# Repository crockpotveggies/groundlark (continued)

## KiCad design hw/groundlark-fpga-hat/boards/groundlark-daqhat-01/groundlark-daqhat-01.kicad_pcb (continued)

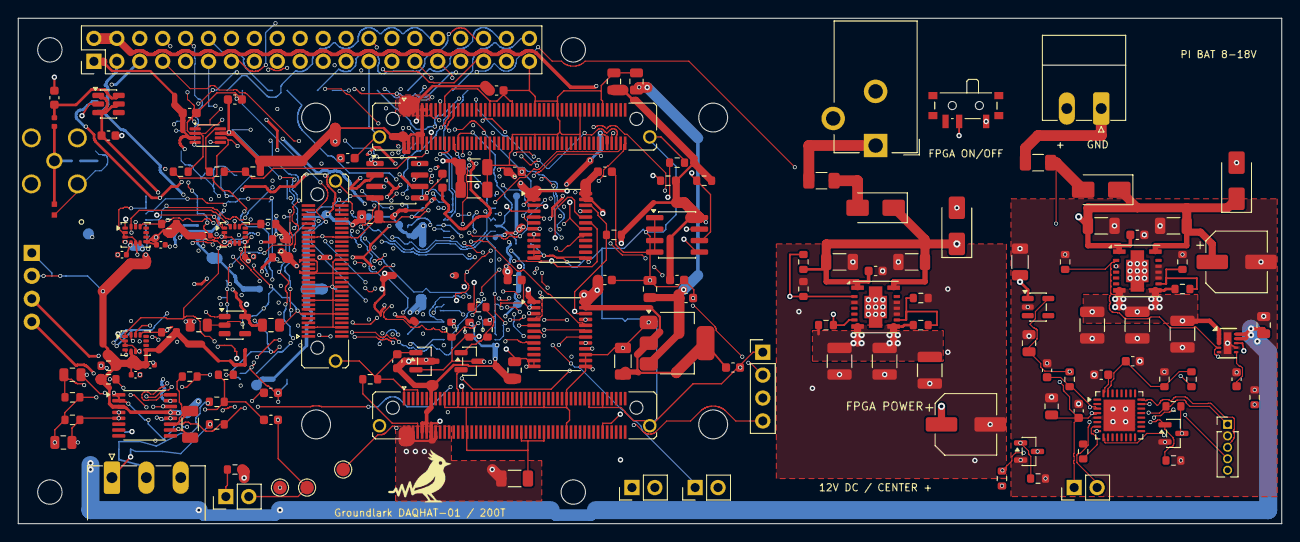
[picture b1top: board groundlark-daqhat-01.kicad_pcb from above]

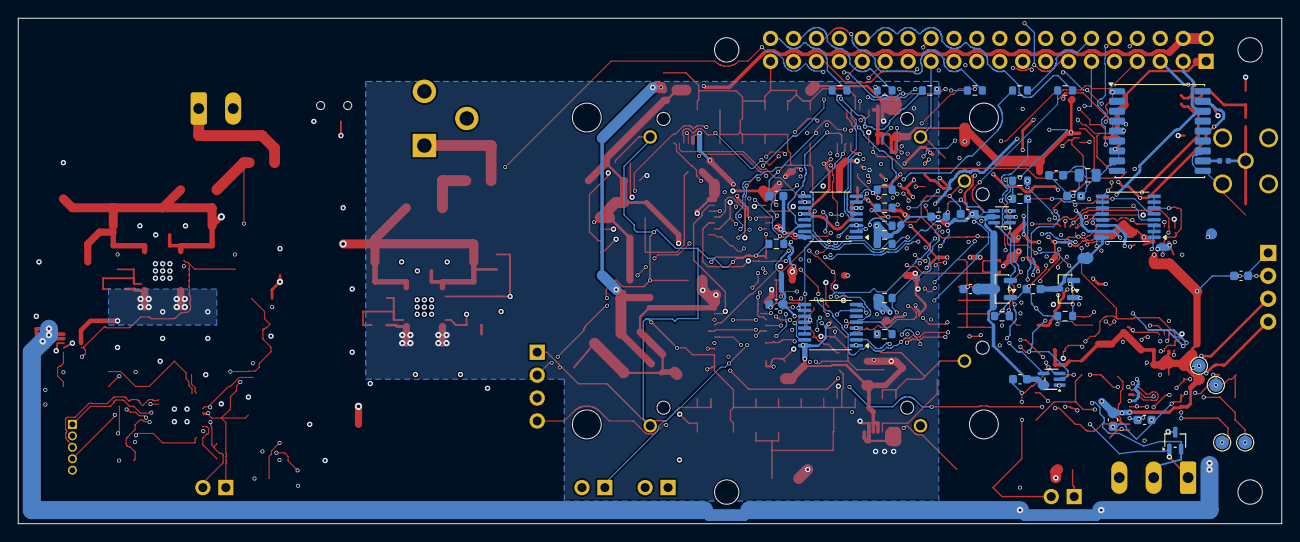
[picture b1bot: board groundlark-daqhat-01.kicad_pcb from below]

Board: 6 copper layers, 140.0 x 56.0 mm, 203 parts (44 on the bottom side), 109 nets.

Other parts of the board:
H1, H2, H3, H4: M2.5 NPTH; MountingHole__MountingHole_2.7mm_M2.5
H80, H81, H82, H83: M3 / 8 mm spacer; TZ_TZ_HOLE

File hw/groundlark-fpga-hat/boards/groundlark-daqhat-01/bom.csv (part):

Reference,Value,MPN,Footprint,DNP,Note
J1,Raspberry Pi 40-pin,Samtec ESQ-120-23-G-D,Connector_PinHeader_2.54mm__PinHeader_2x20_P2.54mm_Vertical,False,"Header land pattern matches bottom mounted socket top-view numbering; tall stack, check Pi 4/5 cooler clearance."
U1,24LC32A,24LC32A-I/SN,Package_SO__SOIC-8_3.9x4.9mm_P1.27mm,False,
R1,3.9k,RC0603FR-073K9L,Resistor_SMD__R_0603_1608Metric,False,
R2,3.9k,RC0603FR-073K9L,Resistor_SMD__R_0603_1608Metric,False,
R3,1k,RC0603FR-071KL,Resistor_SMD__R_0603_1608Metric,False,
JP1,EEPROM write enable,EEPROM write enable,Connector_PinHeader_2.54mm__PinHeader_1x02_P2.54mm_Vertical,False,Fit shunt only while programming ID EEPROM.
C1,100n,GRM188R71H104KA93D,Capacitor_SMD__C_0603_1608Metric,False,
C2,10u,GRM21BR61A106KE19L,Capacitor_SMD__C_0805_2012Metric,False,
C3,10u,GRM21BR61A106KE19L,Capacitor_SMD__C_0805_2012Metric,False,
U11,LSM6DSOTR,LSM6DSOTR,Package_LGA__LGA-14_3x2.5mm_P0.5mm_LayoutBorder3x4y,False,
C12,100n,GRM155R71C104KA88D,Capacitor_SMD__C_0402_1005Metric,False,
C13,100n,GRM155R71C104KA88D,Capacitor_SMD__C_0402_1005Metric,False,
R11,10k,RC0603FR-0710KL,Resistor_SMD__R_0603_1608Metric,False,
U12,LSM6DSOTR,LSM6DSOTR,Package_LGA__LGA-14_3x2.5mm_P0.5mm_LayoutBorder3x4y,False,
C14,100n,GRM155R71C104KA88D,Capacitor_SMD__C_0402_1005Metric,False,
C15,100n,GRM155R71C104KA88D,Capacitor_SMD__C_0402_1005Metric,False,
R12,10k,RC0603FR-0710KL,Resistor_SMD__R_0603_1608Metric,False,
U13,LSM6DSOTR,LSM6DSOTR,Package_LGA__LGA-14_3x2.5mm_P0.5mm_LayoutBorder3x4y,False,
C16,100n,GRM155R71C104KA88D,Capacitor_SMD__C_0402_1005Metric,False,
C17,100n,GRM155R71C104KA88D,Capacitor_SMD__C_0402_1005Metric,False,
R13,10k,RC0603FR-0710KL,Resistor_SMD__R_0603_1608Metric,False,
J4,FPGA test UART/reset,Coldfoot UART service ONLY,Connector_PinHeader_2.54mm__PinHeader_1x04_P2.54mm_Vertical,False,Test points for assembled module UART and active-low reset; do not connect a second driving host.
H1,M2.5 NPTH,M2.5 NPTH,MountingHole__MountingHole_2.7mm_M2.5,False,Nonmagnetic standoffs.
H2,M2.5 NPTH,M2.5 NPTH,MountingHole__MountingHole_2.7mm_M2.5,False,Nonmagnetic standoffs.
H3,M2.5 NPTH,M2.5 NPTH,MountingHole__MountingHole_2.7mm_M2.5,False,Nonmagnetic standoffs.
H4,M2.5 NPTH,M2.5 NPTH,MountingHole__MountingHole_2.7mm_M2.5,False,Nonmagnetic standoffs.
U40,TLV1117LV33DCYR,TLV1117LV33DCYR,Package_TO_SOT_SMD__SOT-223-3_TabPin2,False,
C40,10u,GRM21BR61A106KE19L,Capacitor_SMD__C_0805_2012Metric,False,
C41,100n,GRM188R71H104KA93D,Capacitor_SMD__C_0603_1608Metric,False,
C42,22u,GRM31CR61A226KE19L,Capacitor_SMD__C_1206_3216Metric,False,
C43,100n,GRM188R71H104KA93D,Capacitor_SMD__C_0603_1608Metric,False,
U41,SN74LVC8T245PWR,SN74LVC8T245PWR,Package_SO__TSSOP-24_4.4x7.8mm_P0.65mm,False,
U42,SN74LVC8T245PWR,SN74LVC8T245PWR,Package_SO__TSSOP-24_4.4x7.8mm_P0.65mm,False,
C44,100n,GRM188R71H104KA93D,Capacitor_SMD__C_0603_1608Metric,False,
C45,100n,GRM188R71H104KA93D,Capacitor_SMD__C_0603_1608Metric,False,
C46,100n,GRM188R71H104KA93D,Capacitor_SMD__C_0603_1608Metric,False,
C47,100n,GRM188R71H104KA93D,Capacitor_SMD__C_0603_1608Metric,False,
R50,10k,RC0603FR-0710KL,Resistor_SMD__R_0603_1608Metric,False,
R51,100k,RC0603FR-07100KL,Resistor_SMD__R_0603_1608Metric,False,
U43,ISO1640BDR,ISO1640BDR,Package_SO__SOIC-8_3.9x4.9mm_P1.27mm,False,Power-domain isolation only: grounds are joined. Side-1 VOL max 0.71V requires host VIL >=0.8V; verify Pi revision.
C48,100n,GRM188R71H104KA93D,Capacitor_SMD__C_0603_1608Metric,False,
C49,100n,GRM188R71H104KA93D,Capacitor_SMD__C_0603_1608Metric,False,
R52,4.7k,RC0603FR-074K7L,Resistor_SMD__R_0603_1608Metric,False,
R53,4.7k,RC0603FR-074K7L,Resistor_SMD__R_0603_1608Metric,False,
TP1,SENS_3V3,SENS_3V3,TestPoint__TestPoint_Pad_D1.5mm,False,
TP2,GND,GND,TestPoint__TestPoint_Pad_D1.5mm,False,
TP4,SENSOR_OE_N,SENSOR_OE_N,TestPoint__TestPoint_Pad_D1.5mm,False,
U51,TXU0202DCUR,TXU0202DCUR,Package_SO__VSSOP-8_2.3x2mm_P0.5mm,False,
C75,100n,GRM188R71H104KA93D,Capacitor_SMD__C_0603_1608Metric,False,
C76,100n,GRM188R71H104KA93D,Capacitor_SMD__C_0603_1608Metric,False,
R61,47,RC0603FR-0747RL,Resistor_SMD__R_0603_1608Metric,False,
R62,100k,RC0603FR-07100KL,Resistor_SMD__R_0603_1608Metric,False,
R63,10k,RC0603FR-0710KL,Resistor_SMD__R_0603_1608Metric,False,
U52,TLV803EA30DBZR,TLV803EA30DBZR,Package_TO_SOT_SMD__SOT-23,False,"3.0V falling threshold, 200ms nominal release delay; open-drain output."
C77,100n,GRM188R71H104KA93D,Capacitor_SMD__C_0603_1608Metric,False,
R64,10k,RC0603FR-0710KL,Resistor_SMD__R_0603_1608Metric,False,
Q1,2N7002,2N7002,Package_TO_SOT_SMD__SOT-23,False,Pi GPIO17 HIGH asserts chip reset; does not drive a live voltage into unpowered chip.
R65,1k,RC0603FR-071KL,Resistor_SMD__R_0603_1608Metric,False,
R66,100k,RC0603FR-07100KL,Resistor_SMD__R_0603_1608Metric,False,
J80,LSHM-150-04.0-L-DV-A-S-K-TR,LSHM-150-04.0-L-DV-A-S-K-TR,TZ_TZ100,False,Mates JM1; opposite parity; 8 mm board surface gap
J81,LSHM-150-04.0-L-DV-A-S-K-TR,LSHM-150-04.0-L-DV-A-S-K-TR,TZ_TZ100,False,Mates JM2; opposite parity; 8 mm board surface gap
J82,LSHM-130-04.0-L-DV-A-S-K-TR,LSHM-130-04.0-L-DV-A-S-K-TR,TZ_TZ60,False,Mates JM3; opposite parity; 8 mm board surface gap
JP80,TSW-102-07-G-S,TSW-102-07-G-S,TZ_TZ_JP,False,Fit shunt to DISABLE module; open enables on-board sequence
JP81,TSW-102-07-G-S,TSW-102-07-G-S,TZ_TZ_JP,False,Fit shunt to request module configuration reset
R80,10k,RC0603FR-0710KL,Resistor_SMD__R_0603_1608Metric,False,FPGA JTAG selection / spare CPLD control idle pull-down
R81,10k,RC0603FR-0710KL,Resistor_SMD__R_0603_1608Metric,False,FPGA JTAG selection / spare CPLD control idle pull-down
C80,22u,GRM31CR61A226KE19L,Capacitor_SMD__C_1206_3216Metric,False,Carrier local decoupling; module contains core decoupling
C81,22u,GRM31CR61A226KE19L,Capacitor_SMD__C_1206_3216Metric,False,Carrier local decoupling; module contains core decoupling
C82,22u,GRM31CR61A226KE19L,Capacitor_SMD__C_1206_3216Metric,False,Carrier local decoupling; module contains core decoupling
C83,100n,GRM188R71H104KA93D,Capacitor_SMD__C_0603_1608Metric,False,Carrier local decoupling; module contains core decoupling
C84,4.7u,GRM21BR71A475KA73L,Capacitor_SMD__C_0805_2012Metric,False,Carrier local decoupling; module contains core decoupling
C85,4.7u,GRM21BR71A475KA73L,Capacitor_SMD__C_0805_2012Metric,False,Carrier local decoupling; module contains core decoupling
H80,M3 / 8 mm spacer,M3 / 8 mm spacer,TZ_TZ_HOLE,False,
H81,M3 / 8 mm spacer,M3 / 8 mm spacer,TZ_TZ_HOLE,False,
H82,M3 / 8 mm spacer,M3 / 8 mm spacer,TZ_TZ_HOLE,False,
H83,M3 / 8 mm spacer,M3 / 8 mm spacer,TZ_TZ_HOLE,False,
U22,ADS122C04,ADS122C04IPWR,Package_SO__TSSOP-16_4.4x5mm_P0.65mm,False,"I2C 0x40; internal 2.048V reference, gain 64, normal 330 SPS; unused analog/reference inputs open per TI."
J90,GEO + / - / SHIELD,1803280,"Connector_Phoenix_MC__PhoenixContact_MC_1,5_3-G-3.81_1x03_P3.81mm_Horizontal",False,"Horizontal outward entry (+Y). 1 positive, 2 negative, 3 cable shield. Mate Phoenix 1803581. Never connect power."
D90,TPD2E2U06,TPD2E2U06DCKR,Package_TO_SOT_SMD__SOT-323_SC-70,False,Connector ESD suppression only; not lightning protection.
R90,1k,RC0603FR-071KL,Resistor_SMD__R_0603_1608Metric,False,Matched series input filter / current limiting.
R91,1k,RC0603FR-071KL,Resistor_SMD__R_0603_1608Metric,False,
C90,100n C0G,C3216C0G1H104J160AA,Capacitor_SMD__C_1206_3216Metric,False,C0G differential filter; no piezoelectric X7R on signal path.
C91,1n C0G,C0603C102J5GACTU,Capacitor_SMD__C_0603_1608Metric,False,
C92,1n C0G,C0603C102J5GACTU,Capacitor_SMD__C_0603_1608Metric,False,
R92,1M,RC0603FR-071ML,Resistor_SMD__R_0603_1608Metric,False,
R93,1M,RC0603FR-071ML,Resistor_SMD__R_0603_1608Metric,False,
R94,10k,RC0603FR-0710KL,Resistor_SMD__R_0603_1608Metric,False,
R95,10k,RC0603FR-0710KL,Resistor_SMD__R_0603_1608Metric,False,
C93,10u,GRM21BR61A106KE19L,Capacitor_SMD__C_0805_2012Metric,False,Filtered mid-supply; sensor has no excitation current source.
R96,22,RC0603FR-0722RL,Resistor_SMD__R_0603_1608Metric,False,
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
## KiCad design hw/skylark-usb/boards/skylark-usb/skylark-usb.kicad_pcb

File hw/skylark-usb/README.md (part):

# Skylark USB — Rev A

Skylark is the Groundlark project's outdoor air-quality accessory. Its **90 × 100 mm,
four-layer PCB** mounts vertically inside a ventilated, downward-open hood. Two
removable gas cells face the sheltered air space. A separate PMS5003 sits beside
the board, with its sampling face toward the bottom grille.

The front silkscreen carries the 7 mm Groundlark favicon above the Skylark title.

The atopile circuit, routed KiCad board, review schematic and BOM are implemented.
This is an **engineering prototype**, with [STM32 firmware](../../sw/skylark/README.md)
and shared simulation/tests implemented. Calibration and physical
qualification remain pending; it is not a fabrication release or a validated
volcanic warning instrument. No camera, Pi HAT or separate sensor daughterboard is included.

## Hardware

| Function | Implementation |
| --- | --- |
| USB | USB-C, USB 2.0 full speed; STM32F072CBT6 with internal USB clock |
| SO₂ | SGX-7SO2-AQ-20, separate working/auxiliary TIAs, 100 kΩ feedback |
| H₂S | SGX-7H2S-AQ-25, separate working/auxiliary TIAs, 20 kΩ feedback |
| Gas conversion | ADS122C04, external REF3025 reference, four independent ADC inputs |
| Analog circuits | OPA387/OPA2387, switched analog supply, buffered 1.25 V electrode reference, compensated potentiostats, power-off electrode clamps |
| Particles | External PMS5003; protected switched 5 V supply, UART, sleep/reset control |
| Temperature/humidity | Filtered SHT40-AD1F-R2, I²C 0x44, on a slotted PCB finger near the lower ventilation |
| Pressure | BMP388, I²C 0x76 |
| Debug/service | 10-pin 1.27 mm SWD, reset/boot buttons, status LED and seven rail test pads |

Gas channels use 20 Ω electrode loads and 0.1%, 25 ppm/K thin-film gain resistors.
SO₂ feedback is 100 kΩ/100 nF; H₂S feedback is 20 kΩ/500 nF (five parallel
100 nF capacitors). Feedback and potentiostat compensation use C0G dielectric
to avoid the piezoelectric behavior of high-permittivity ceramic capacitors.
Each ADC input has a 10 kΩ/10 µF filter placed beside the ADC. Both gases have
a nominal 15.9 Hz feedback pole and a 1.59 Hz output pole. Together they attenuate a 50 Hz input signal
by about 40.3 dB before the ADC's digital filtering. These calculations omit cell
impedance, capacitor bias/temperature effects and amplifier noise gain; they
do not establish loop stability or a noise floor. Preserve matching WE/AE filters.

OPA387/OPA2387 specifies 177 nV peak-to-peak input noise over 0.1–10 Hz. Short,
via-free summing traces, local feedback and bypass returns reduce avoidable
pickup. The ADS122C04's typical ±5 nA bypass-mode input current can produce
about ±50 µV across 10 kΩ; this is a typical error estimate, not a guaranteed
bound. Measure channel offset and its drift, and retain calibration metadata.

Both outer faces have guard copper driven from the 1.25 V reference through
100 Ω R75. Exposed guard arcs surround the working, reference and auxiliary
socket pads; gaps allow signal traces to exit. Cleanliness remains essential:
4 nA of parasitic current mimics 10 ppb SO₂ at nominal sensitivity. Qualify
residual leakage after assembly, cleaning and coating, including humid soak
and fan-on/fan-off tests. Mask and coating alone do not establish that limit.

Both reference and working electrodes are nominally at 1.25 V;
this is a **zero-bias assumption**. SGX's public AQ datasheets do not unambiguously
specify bias for both exact variants. Obtain SGX confirmation before releasing
the circuit for fabrication. The manufacturer cell drawing is a bottom view;
the PCB socket pattern explicitly mirrors it.

Nominal sensitivity is 40 mV/ppm for SO₂ and 34 mV/ppm for H₂S. At the published
maximum sensitivity, full-scale gas excursions are approximately 1.00 V and
1.05 V around 1.25 V, respectively. These are headroom calculations, not detection
limits. Preserve raw WE and AE readings; compensation coefficients and baseline
calibration must come from measurements for each cell. A 24-bit ADC does not
establish ppb-level system accuracy.

## Assembly and installation

The [Skylark procurement registry](../assembly/skylark-usb/jlcpcb-parts.json)
covers all 119 PCB assembly placements in 37 exact manufacturer/catalog groups,
with dated stock observations in the registry. The current assembly uses
HRO TYPE-C-31-M-12 / C165948, Yageo RC0603FR-0782KL / C137678 and Bosch
BMP388 / C779278. These replacements were available without preorder, with a
minimum quantity of one, on 2026-09-28 UTC. Public stock is not reserved stock.
C2 retains its documented 16 V Murata 4.7 µF procurement substitution.

The [assembly guide](../assembly/skylark-usb/README.md) describes the read-only
Gerber/BOM/CPL exporter and manual parts. All 119 placements pass the numbered
supplier-pad fit, including explicit bottom-side handling. The HRO footprint
uses the manufacturer's 2020-12-08 drawing, shared power lands and plated shell
slots. Gas cells, eight sockets and the PMS5003 harness are assembled separately.
Recheck stock and both sides of the actual order preview before purchasing.

- Order JLCPCB's standard **1.6 mm, four-layer FR-4, JLC04161H-7628** stack:
  1 oz outer copper and 0.5 oz inner copper, with both inner layers assigned to
  ground. The recorded dielectric thicknesses are 0.2104 / 1.065 / 0.2104 mm.
  Use ENIG and conventional tented **0.60/0.30 mm through-vias** outside SMT pads.
  Minimum track/clearance is 0.15 mm. This design does not require HDI, blind or
  buried vias, filled/capped vias, or custom lamination. The stack comes from
  [JLCPCB's stock table](https://jlcpcb.com/impedance); USB signal integrity still
  requires a physical check. The selection does not imply an impedance guarantee.
- Fit **eight Mill-Max 0322-0-15-15-34-27-10-0 sockets** before inserting the cells.
  Finished socket holes are 2.35 mm nominal. The contact range covers the SGX
  1.00 ± 0.15 mm pins. Do not solder the gas cells directly. Check actual insertion
  and retention using purchased parts; provide a removable enclosure retainer.
- Gas-cell bodies are Ø31.5 × 15.5 mm. With the socket rim 4.88 mm above the PCB
  seating surface (including its 0.81 mm flange), allow at least 20.38 mm on the cell side, plus assembly tolerance and airflow
  clearance. The centers are 42 mm apart. Keep sensor faces clear.
- Four 3.2 mm mounting holes are at (4,4), (86,4), (4,96), (86,55) mm from the
  upper-left outline corner. USB and the temperature-sensor finger face down.
  The PMS5003 needs its own cradle and cable restraint.
- J2 is a **JST GH 8-pin board connector**. A harness must map its numbered pins
  to the PMS5003; do not assume an arbitrary supplied PMS cable mates with this
  header or preserves wire order.
- Clean and dry the PCB before installing cells. Conformal coating must exclude
  gas-cell faces and socket contacts, the SHT40 filter, BMP388 pressure port,
  connectors, buttons and service pads. Follow manufacturer assembly instructions;
  do not wash the installed humidity sensor or seal its filter.
- The hood provides rain shielding while admitting ambient air. Coating is an
  additional protection measure, not a waterproof enclosure. Avoid trapped water,
  direct spray, insects and condensation. Keep the PMS exhaust away from the
  temperature sensor and allow passive air exchange around both gas cells.

| J2 pin | Signal | Direction relative to Skylark |
| --- | --- | --- |
| 1 | Switched 5 V | Output |
| 2 | Ground | Return |
| 3 | PMS SET, low for sleep | Open-drain control |
| 4 | PMS RX | UART output to sensor |
| 5 | PMS TX | UART input from sensor |
| 6 | PMS RESET, active low | Open-drain control |
| 7, 8 | Reserved | Deliberately unconnected |

## Power and firmware requirements

The [prototype STM32 firmware](../../sw/skylark/README.md) implements sensor
readout, USB streaming and power sequencing. Its image builds and native fault
tests pass; the following physical power/timing checks remain required.

The PMS rail defaults off. Firmware must enumerate and obtain its configured USB
power allocation before enabling it. The 82 kΩ TPS2553 setting gives approximately
284–369 mA current-limit bounds including resistor tolerance, with 323 mA nominal.
Budget another 50 mA for the controller and supporting circuits; the configured
envelope stays below 500 mA. Measure fan startup, fuse drop and actual consumption;
these are design bounds, not bench results. See the [power supply guide](../../docs/power-supplies.md)
for allocations, cable-voltage cases, attach charge, regulator dissipation and
suspend limits. The analog rail has an 8 mA design
budget. The 22 Ω supply filter leaves at least 3.05 V using the stated regulator
and resistor limits; measure this rail over supply and temperature.

The PMS5003 requires at least 4.5 V at its supply. This board does not boost a low
USB voltage. Use a suitable 5 V source and short cable, verify J2 under load, and
invalidate PM measurements on undervoltage or switch fault. The MCU measures the
post-fuse USB rail through a 2:1 divider. Keep the PMS UART output low or high
impedance while that sensor is unpowered to prevent backfeed. Suspend handling
must turn off the PMS and the analog rail, disable the status LED, and put the
MCU and remaining sensors into suitable low-power states. Measure total current
against the applicable USB suspend budget.

The analog rail defaults off through U13 (TPS22918); electrode clamps default
engaged through Q7. PB12 drives ANA_EN, and PB13 drives CLAMP_HOLD (high engages
the clamps). Keep CLAMP_HOLD high while enabling ANA_EN; after the rail and
reference settle, drive CLAMP_HOLD low to release the clamps. Before disabling
ANA_EN, stop conversions and drive CLAMP_HOLD high. Do not sample until the cell
baseline has settled after restarting. Qualify this sequence, reset/brownout
behavior and the clamp gate voltage on hardware. The 10 nF CT capacitor controls
switch slew; firmware timing must account for the measured rail/reference rise.

Q7 is an MMBT3904 with its emitter at VZERO, so an engaged clamp follows the
electrode reference instead of pulling the JFET gates below powered electrodes.
R74 limits base current. D4 isolates the gate pull-up from a falling USB rail;
R71 returns the gate toward VZERO when that supply disappears. Q1–Q4 are
MMBFJ270 devices, specified at 200 pA maximum gate leakage at 25 °C under the
datasheet test conditions. This is not an outdoor-temperature leakage guarantee.
Check gate-to-electrode voltage and discharge behavior during slow ramps,
hard disconnects, MCU reset and brownout with real cells attached.

Sensor power follows USB configuration and suspend state. Closing a CDC data
session leaves the gas bias active; reopening does not repeat conditioning.
The firmware's 60-second gas suppression is a minimum prototype policy. It does
not certify a stable baseline; field software must apply a qualified settling
and calibration policy before interpreting raw readings as gas concentrations.

Use ADS122C04 address 0x40, gain 1, PGA bypassed and the external 2.5 V reference.
Multiplex AIN0–3 as single-ended SO₂ WE, SO₂ AE, H₂S WE, H₂S AE. Start with normal
330 SPS single-shot conversion mode. Eight-millisecond service slots give a
nominal 32 ms period per electrode (31.25 samples/s). The scheduler budgets
100 kHz I²C transactions and enforces a separate five-tick minimum after a new
conversion starts. Service delays extend the schedule rather than restarting
unfinished conversions. Maintain cell bias during normal operation and treat
power-up settling as missing data.

The 15.9 Hz feedback pole and 1.59 Hz output pole provide approximately 33 dB
nominal attenuation at 31.25 Hz. The output filters use 10 kΩ / 10 µF; effective
capacitance under voltage, temperature and aging must be measured. All original
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
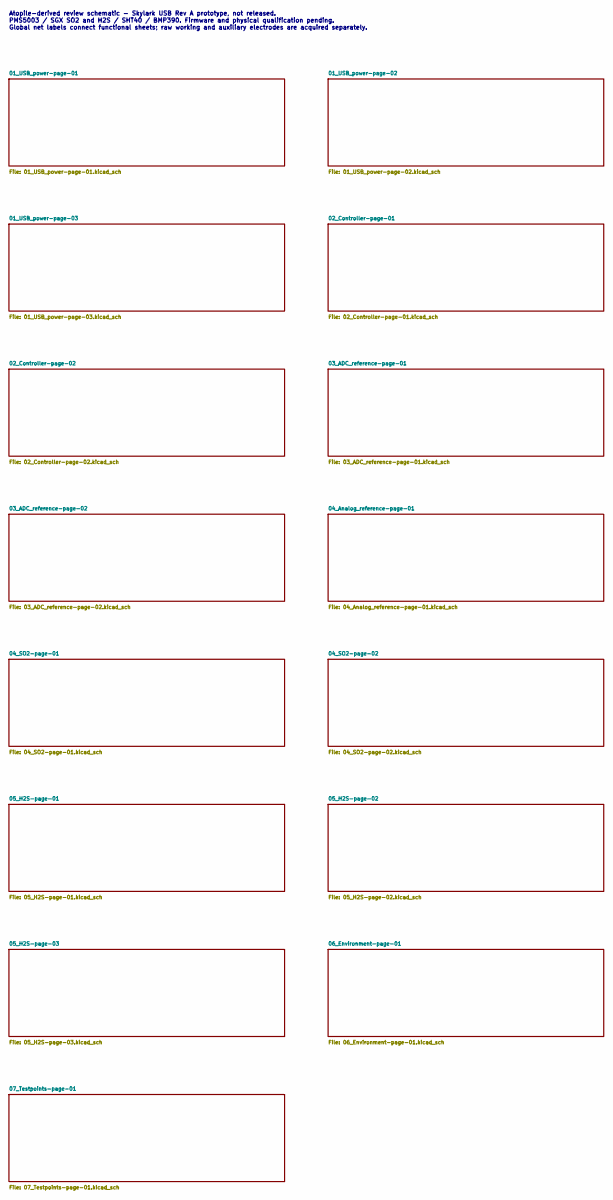
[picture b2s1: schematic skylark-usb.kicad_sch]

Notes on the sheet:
Atopile-derived review schematic - Skylark USB Rev A prototype, not released. PMS5003 / SGX SO2 and H2S / SHT40 / BMP390. Firmware and physical qualification pending. Global net labels connect functional sheets; raw working and auxiliary electrodes are acquired separately.

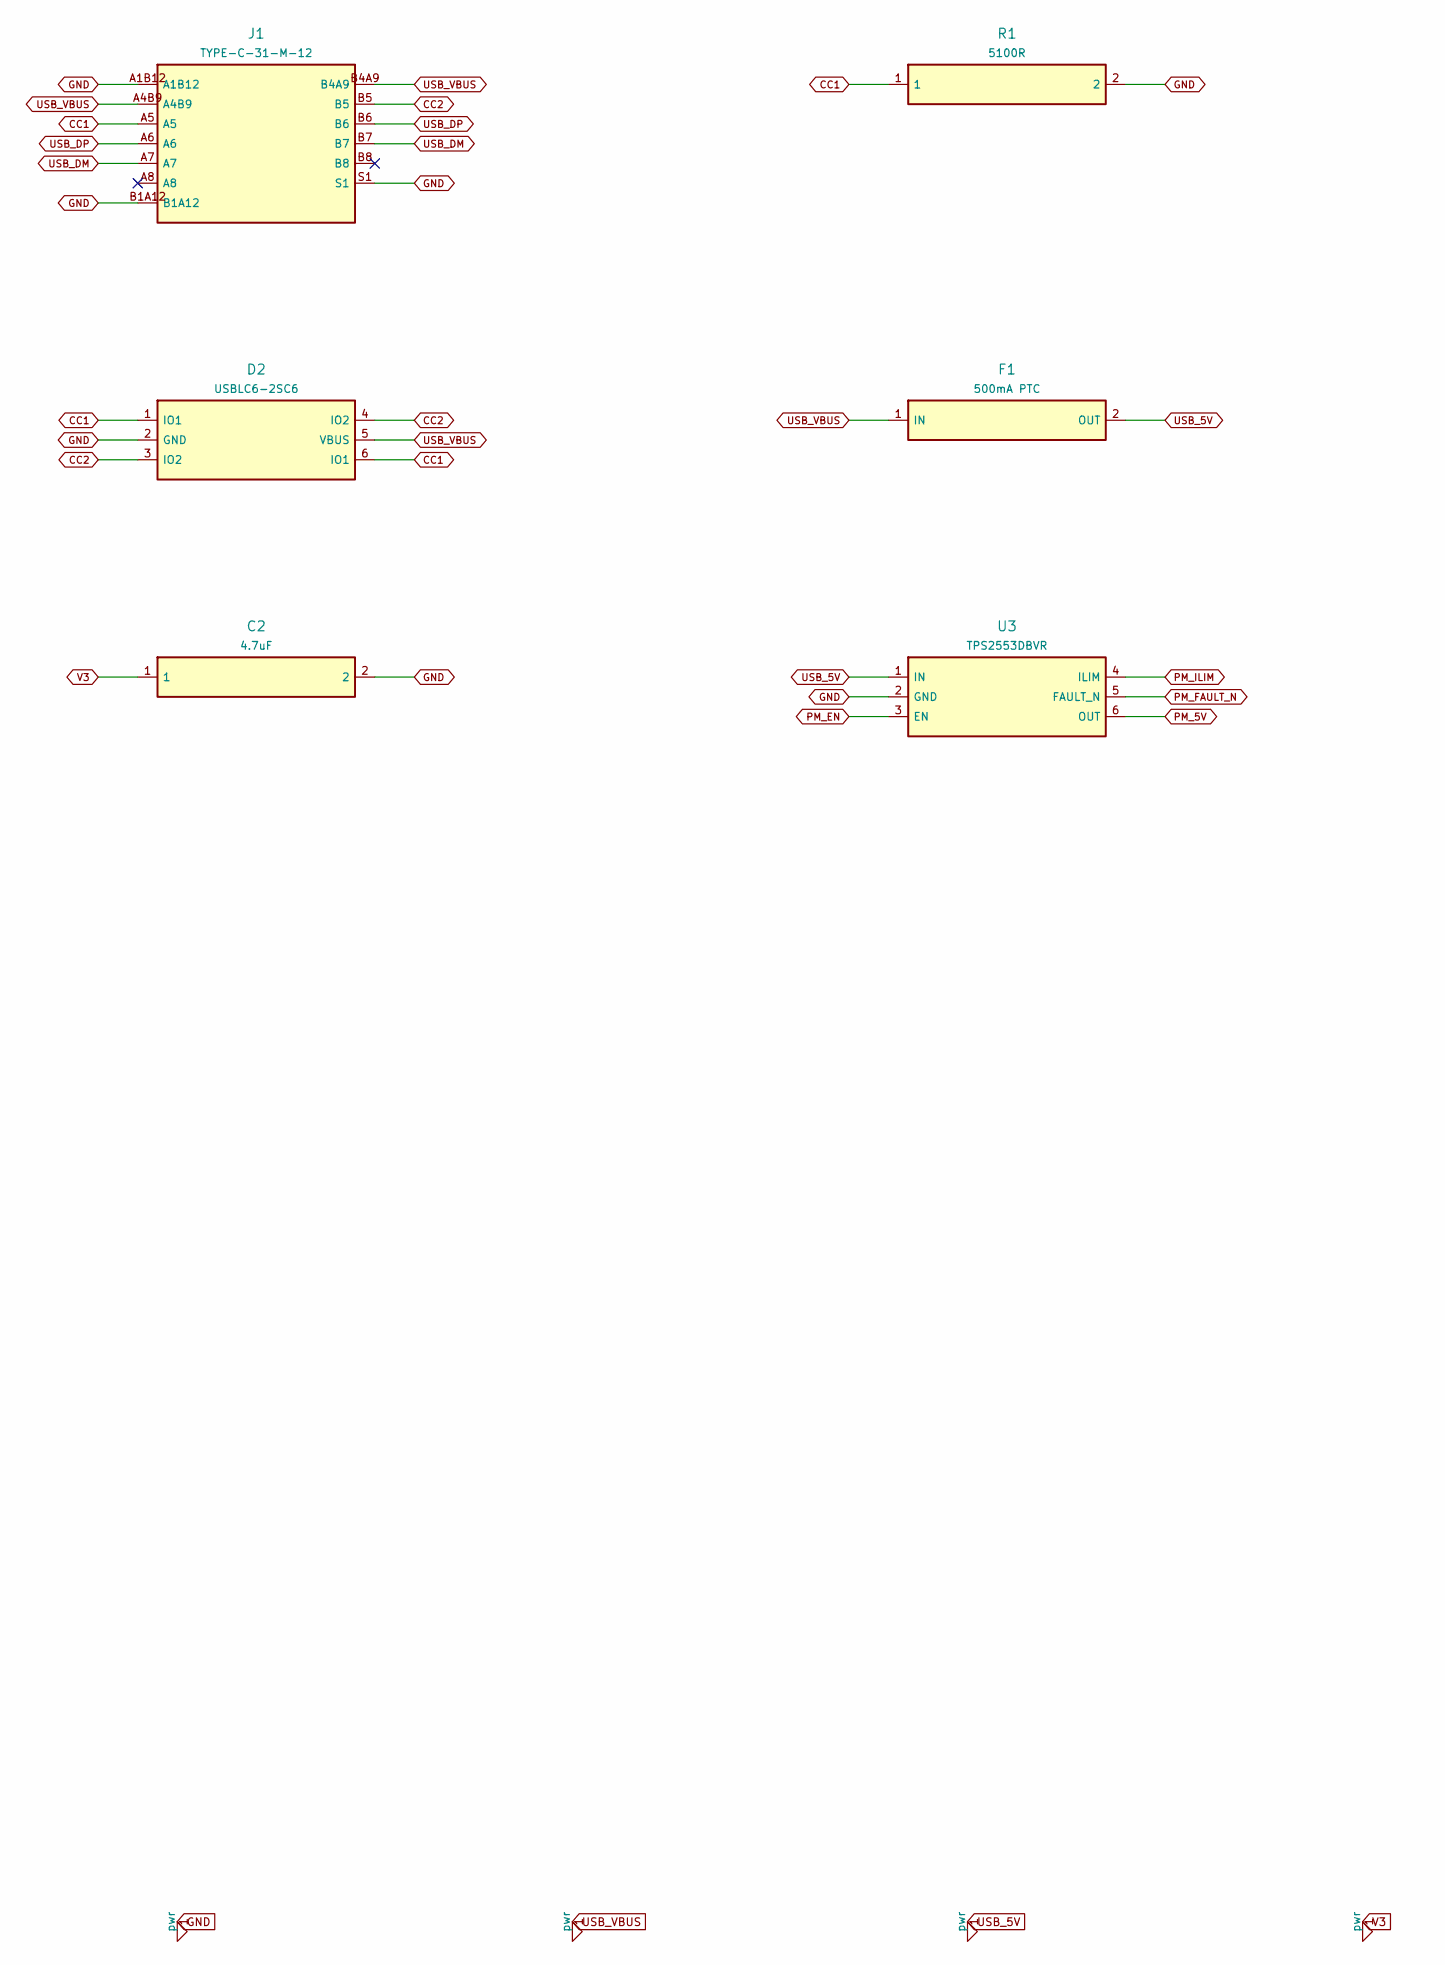
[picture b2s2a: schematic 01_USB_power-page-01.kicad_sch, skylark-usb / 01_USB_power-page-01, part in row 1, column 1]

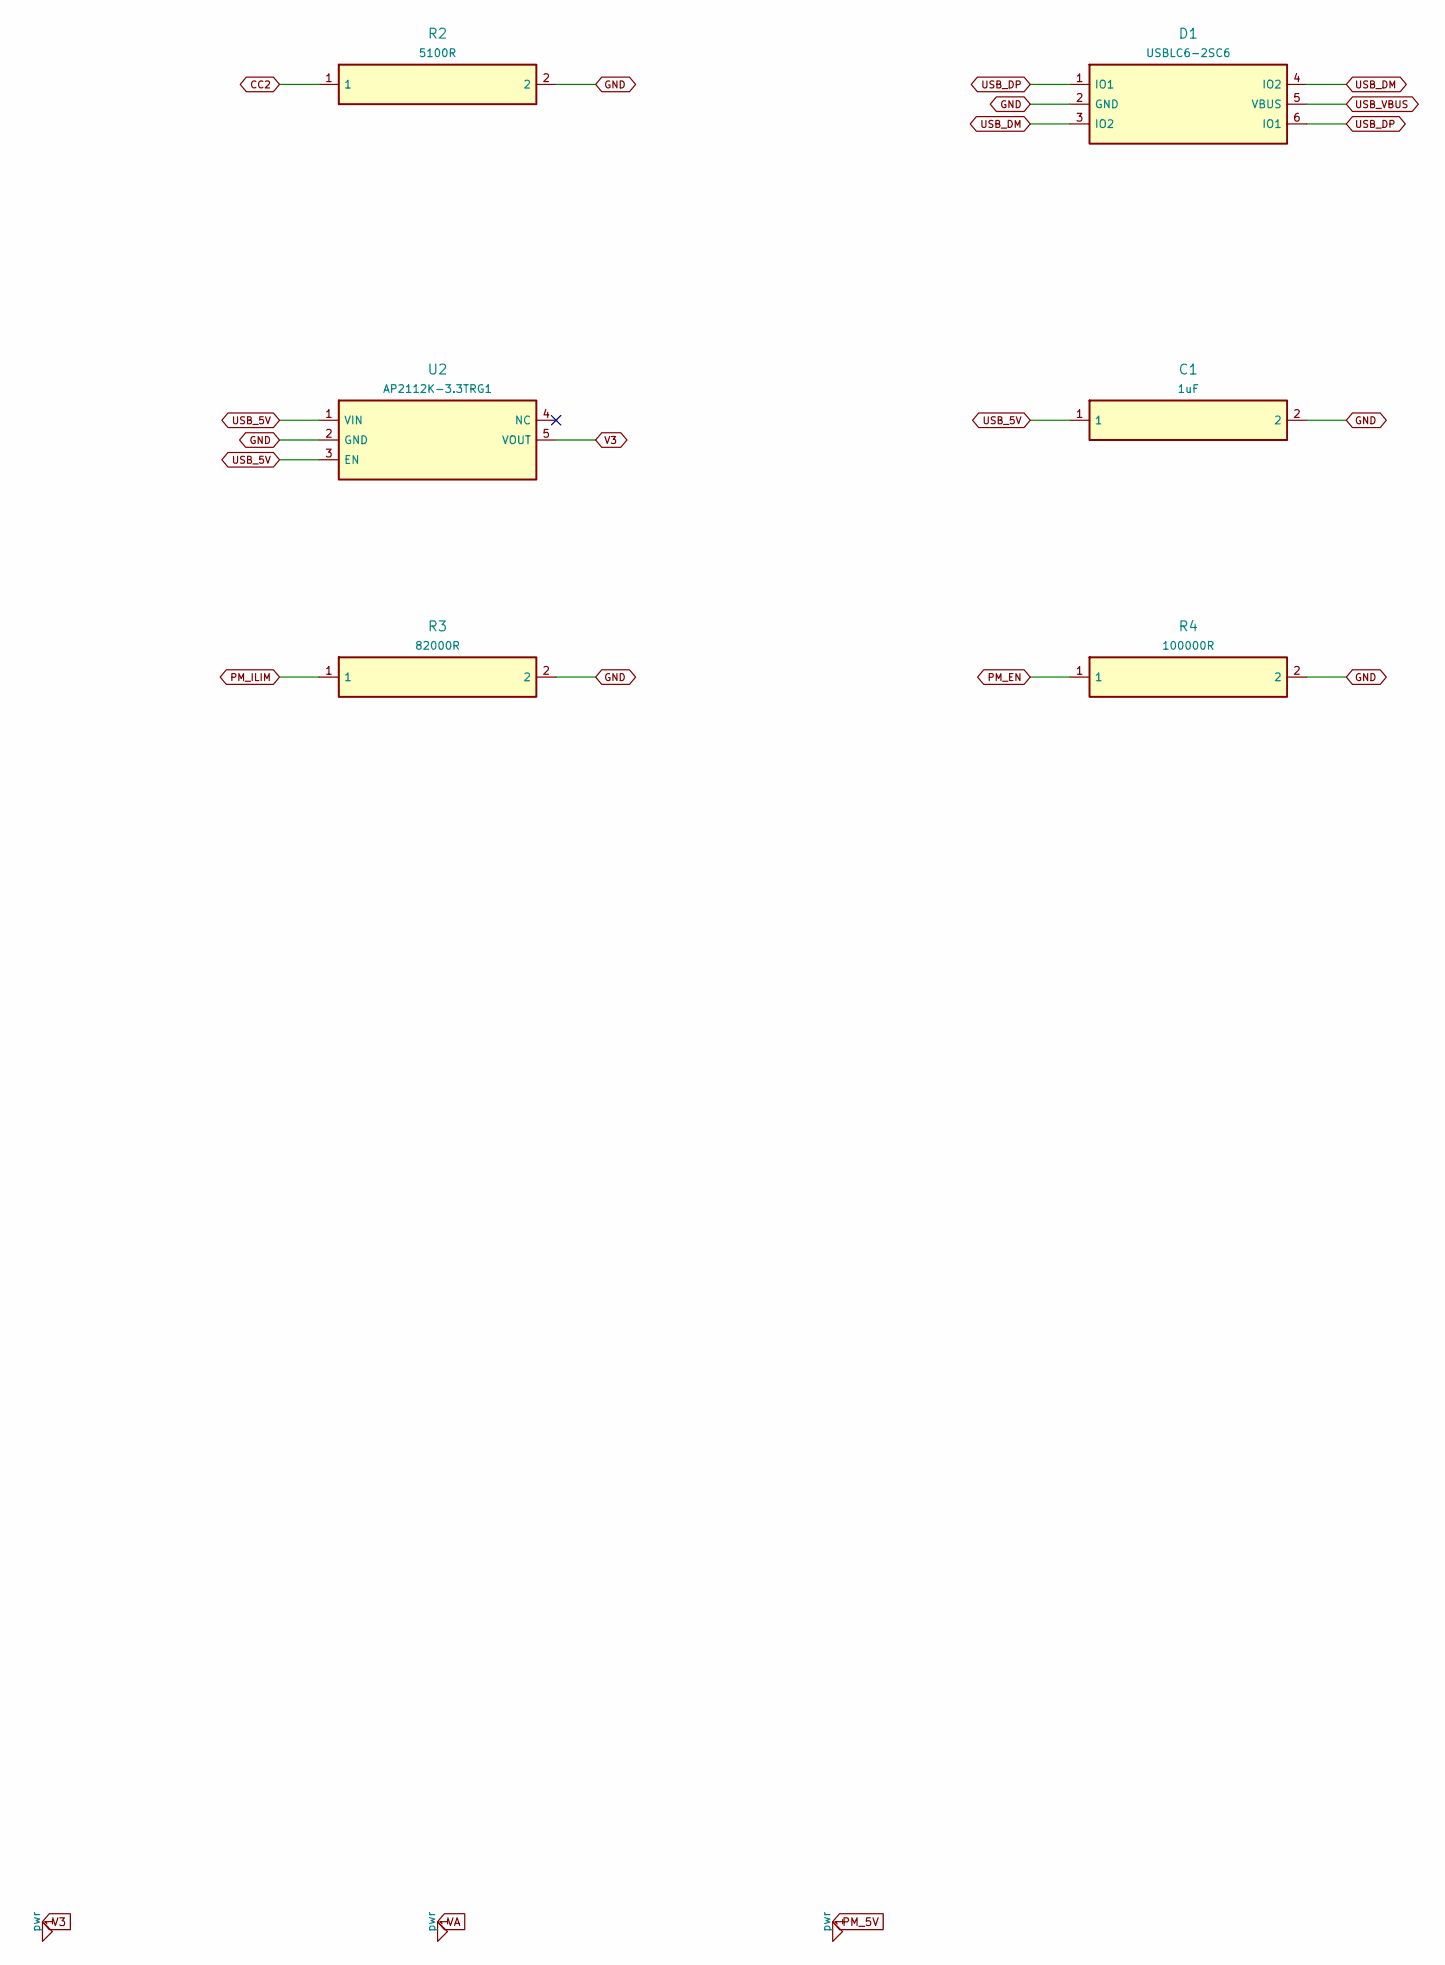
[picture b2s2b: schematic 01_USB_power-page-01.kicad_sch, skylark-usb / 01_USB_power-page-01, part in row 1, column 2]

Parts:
C1: 1uF; Capacitor_SMD__C_0603_1608Metric; MPN GRM188R71E105KA12D
C2: 4.7uF; Capacitor_SMD__C_0805_2012Metric; MPN GRM21BR71A475KA73L
D1, D2: USBLC6-2SC6; Package_TO_SOT_SMD__SOT-23-6; MPN USBLC6-2SC6
F1: 500mA PTC; Fuse_1206; MPN 1206L050YR
J1: TYPE-C-31-M-12; USB_C_HRO_TYPE-C-31-M-12; MPN TYPE-C-31-M-12
R1, R2: 5100R; Resistor_SMD__R_0603_1608Metric; MPN RC0603FR-075K1L
R3: 82000R; Resistor_SMD__R_0603_1608Metric; MPN RC0603FR-0782KL
R4: 100000R; Resistor_SMD__R_0603_1608Metric; MPN RT0603BRD07100KL
U2: AP2112K-3.3TRG1; Package_TO_SOT_SMD__SOT-23-5; MPN AP2112K-3.3TRG1
U3: TPS2553DBVR; Package_TO_SOT_SMD__SOT-23-6; MPN TPS2553DBVR

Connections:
A8: J1.A8
B8: J1.B8
CC1: D2.1 (IO1), D2.6 (IO1), J1.A5, R1.1
CC2: D2.3 (IO2), D2.4 (IO2), J1.B5, R2.1
GND: C1.2, C2.2, D1.2 (GND), D2.2 (GND), J1.A1B12, J1.B1A12, J1.S1, R1.2, R2.2, R3.2, R4.2, U2.2 (GND), U3.2 (GND); also elsewhere on the board
PM_5V: U3.6 (OUT); also elsewhere on the board
PM_EN: R4.1, U3.3 (EN); also elsewhere on the board
PM_FAULT_N: U3.5 (FAULT_N); also elsewhere on the board
PM_ILIM: R3.1, U3.4 (ILIM)
USB_5V: C1.1, F1.2 (OUT), U2.1 (VIN), U2.3 (EN), U3.1 (IN); also elsewhere on the board
USB_DM: D1.3 (IO2), D1.4 (IO2), J1.A7, J1.B7; also elsewhere on the board
USB_DP: D1.1 (IO1), D1.6 (IO1), J1.A6, J1.B6; also elsewhere on the board
USB_VBUS: D1.5 (VBUS), D2.5 (VBUS), F1.1 (IN), J1.A4B9, J1.B4A9
V3: C2.1, U2.5 (VOUT); also elsewhere on the board
u2-4: U2.4 (NC)

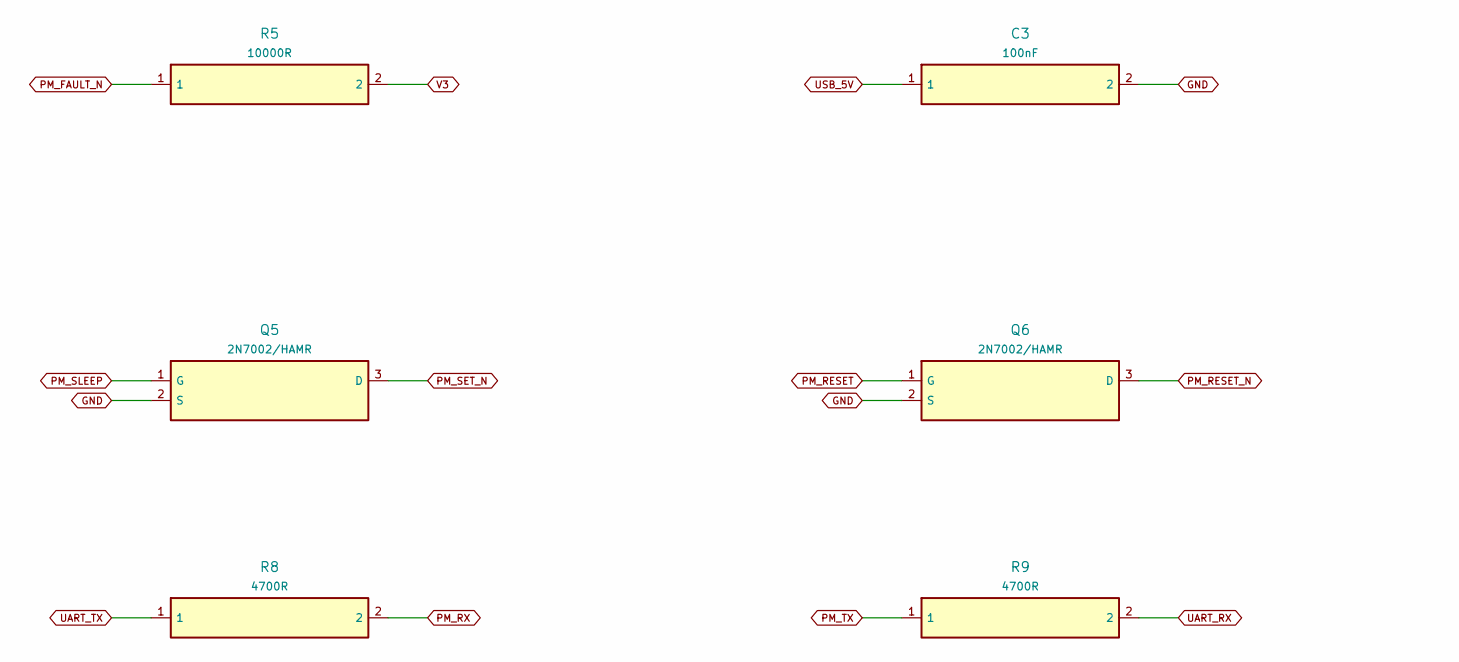
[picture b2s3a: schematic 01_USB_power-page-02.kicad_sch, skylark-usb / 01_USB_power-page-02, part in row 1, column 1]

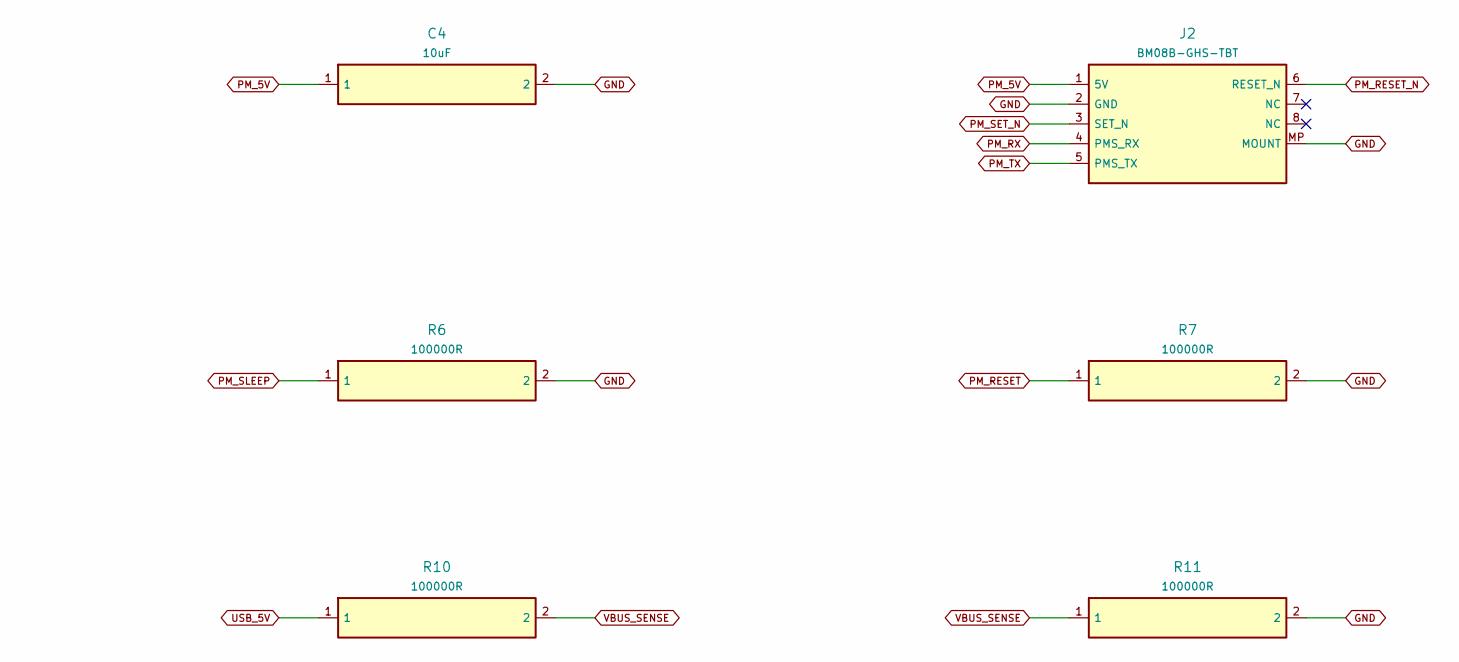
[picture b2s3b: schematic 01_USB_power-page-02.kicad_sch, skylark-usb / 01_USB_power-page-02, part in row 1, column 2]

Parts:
C3: 100nF; Capacitor_SMD__C_0603_1608Metric; MPN GRM188R71H104KA93D
C4: 10uF; Capacitor_SMD__C_0805_2012Metric; MPN GRM21BR61A106KE19L
J2: BM08B-GHS-TBT; Connector_JST__JST_GH_BM08B-GHS-TBT_1x08-1MP_P1.25mm_Vertic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; MPN BM08B-GHS-TBT
Q5, Q6: 2N7002/HAMR; Package_TO_SOT_SMD__SOT-23; MPN 2N7002/HAMR
R5: 10000R; Resistor_SMD__R_0603_1608Metric; MPN RT0603BRD0710KL
R6, R7, R10, R11: 100000R; Resistor_SMD__R_0603_1608Metric; MPN RT0603BRD07100KL
R8, R9: 4700R; Resistor_SMD__R_0603_1608Metric; MPN RC0603FR-074K7L

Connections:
7: J2.7 (NC)
8: J2.8 (NC)
GND: C3.2, C4.2, J2.2 (GND), J2.MP (MOUNT), Q5.2 (S), Q6.2 (S), R6.2, R7.2, R11.2; also elsewhere on the board
PM_5V: C4.1, J2.1 (5V); also elsewhere on the board
PM_FAULT_N: R5.1; also elsewhere on the board
PM_RESET: Q6.1 (G), R7.1; also elsewhere on the board
PM_RESET_N: J2.6 (RESET_N), Q6.3 (D)
PM_RX: J2.4 (PMS_RX), R8.2
PM_SET_N: J2.3 (SET_N), Q5.3 (D)
PM_SLEEP: Q5.1 (G), R6.1; also elsewhere on the board
PM_TX: J2.5 (PMS_TX), R9.1
UART_RX: R9.2; also elsewhere on the board
UART_TX: R8.1; also elsewhere on the board
USB_5V: C3.1, R10.1; also elsewhere on the board
V3: R5.2; also elsewhere on the board
VBUS_SENSE: R10.2, R11.1; also elsewhere on the board

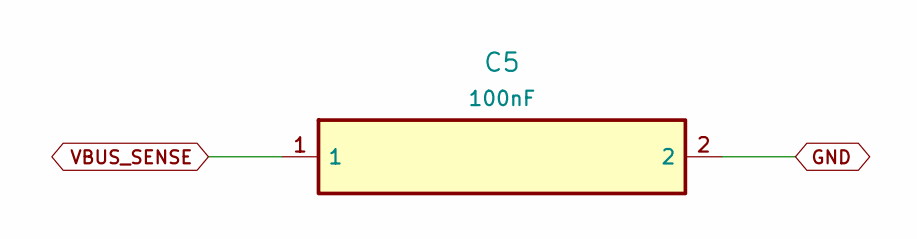
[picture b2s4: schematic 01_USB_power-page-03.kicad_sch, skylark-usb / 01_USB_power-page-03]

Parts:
C5: 100nF; Capacitor_SMD__C_0603_1608Metric; MPN GRM188R71H104KA93D

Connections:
GND: C5.2; also elsewhere on the board
VBUS_SENSE: C5.1; also elsewhere on the board

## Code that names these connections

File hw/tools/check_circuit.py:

"""Independent circuit invariants against the actual atopile-compiled PCB."""
from pathlib import Path
from project_paths import compiled_dir, load_layout
from burrowlark_checks import population
import argparse,json,re
import pcbnew as p
ROOT=Path(__file__).resolve().parents[2]
def require(pins,ref,expected):
    for pin,net in expected.items():
        assert pins.get((ref,str(pin)))==net,(ref,pin,pins.get((ref,str(pin))),net)
def main(boards=('groundlark-field-head',)):
    metadata=load_layout(*boards);source=(ROOT/'hw/shared/elec/parts.ato').read_text() + '\n' + (ROOT/'hw/shared/elec/burrowlark.ato').read_text()
    blocks={m[1]:m[2] for m in re.finditer(r'^component (\w+):\n(.*?)(?=^component |\Z)',source,re.M|re.S)}
    reports=[]
    for name,meta in metadata.items():
        target='field_head';b=p.LoadBoard(str(compiled_dir(target)/(target+'.kicad_pcb')))
        pins={(f.GetReference(),pad.GetNumber()):pad.GetNetname() for f in b.GetFootprints() for pad in f.Pads() if pad.GetNumber()}
        for part in meta['parts']:
            if not part['type']:continue
            block=blocks[part['type']]
            assert f'partnumber="{part["mpn"]}"' in block,(part['ref'],'BOM/source MPN mismatch')
            assert f'footprint="{part["local_fp"]}.kicad_mod"' in block,(part['ref'],'BOM/source footprint mismatch')
        require(pins,'U2',{1:'SCL',2:'GND',3:'SDA',4:'GND',5:'MAG_DRDY',7:'GND',10:'V3_SENSOR',12:'V3_SENSOR',13:'V3_SENSOR',14:'GND'})
        population(f.GetReference() for f in b.GetFootprints())
        population(part['ref'] for part in meta['parts'])
        require(pins,'U1',{1:'V3',5:'V3',16:'GND',17:'V3',32:'GND',4:'NRST',6:'SENSOR_EN',14:'MAG_DRDY',21:'USB_DM',22:'USB_DP',23:'SWDIO',24:'SWCLK',29:'SCL',30:'SDA',31:'BOOT0'})
        require(pins,'J1',{'A5':'USB_CC1','B5':'USB_CC2','A6':'USB_DP','B6':'USB_DP','A7':'USB_DM','B7':'USB_DM','A4':'USB_VBUS','A9':'USB_VBUS','B4':'USB_VBUS','B9':'USB_VBUS','A1':'GND','A12':'GND','B1':'GND','B12':'GND','S1':'GND'})
        require(pins,'R1',{1:'USB_CC1',2:'GND'});require(pins,'R2',{1:'USB_CC2',2:'GND'})
        require(pins,'F1',{1:'USB_VBUS',2:'USB_5V'})
        require(pins,'U4',{1:'USB_5V',2:'GND',3:'USB_5V',5:'V3'})
        require(pins,'U5',{1:'V3',2:'GND',3:'SENSOR_EN',5:'V3_SENSOR',6:'V3_SENSOR'})
        require(pins,'R5',{1:'SENSOR_EN',2:'GND'})
        require(pins,'C1',{1:'USB_5V',2:'GND'})
        require(pins,'C8',{1:'NRST',2:'GND'})
        for n in [2,3,6,7,9]:require(pins,f'C{n}',{1:'V3',2:'GND'})
        require(pins,'C4',{1:'V3_SENSOR',2:'GND'})
        from burrowlark_checks import climate_pins
        climate_pins(pins)
        reports.append({'board':name,'compiled_pins':len(pins),'source_bom_agreement':'PASS','circuit_invariants':'PASS'})
    result={'boards':reports,'negative_mutations':[]}
    (ROOT/'hw/shared/simulation/circuit-checks.json').write_text(json.dumps(result,indent=2))
    print(json.dumps(result,indent=2))
if __name__=='__main__':
    parser=argparse.ArgumentParser(description=__doc__)
    parser.add_argument('--board',choices=('groundlark-field-head',))
    args=parser.parse_args()
    main((args.board,) if args.board else ('groundlark-field-head',))

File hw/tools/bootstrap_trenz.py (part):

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
part('J83','TZ_POWER','1715721','TerminalBlock_Phoenix','TerminalBlock_Phoenix_MKDS-1,5-2-5.08_1x02_P5.08mm_Horizontal',[137.5,9],{1:'EXT_3V3',2:'GND'},angle=90,note='REGULATED 3.3 V ONLY; current-limited external supply, 3 A initial operating budget')
part('F80','TZ_FUSE','0467005.NR','Fuse','Fuse_1206_3216Metric',[127,4],{1:'EXT_3V3',2:'FPGA_VIN'},note='5 A fast fuse; not reverse-polarity or overvoltage protection')
part('J84','TZ_JTAG','TSW-106-07-G-S','Connector_PinHeader_2.54mm','PinHeader_1x06_P2.54mm_Vertical',[135,22],{1:'JTAG_TMS',2:'JTAG_TDI',3:'JTAG_TDO',4:'JTAG_TCK',5:'GND',6:'FPGA_3V3'},note='Digilent 6-pin JTAG signal order; reference is an output, not a power input')
part('J85','TZ_AUX','TSW-103-07-G-D','Connector_PinHeader_2.54mm','PinHeader_2x03_P2.54mm_Vertical',[111,26],{1:'FPGA_AUX0',2:'GND',3:'FPGA_AUX1',4:'GND',5:'FPGA_AUX2',6:'GND'},note='3.3 V spare I/O; fit cable before stacking')
part('JP80','TZ_JP','TSW-102-07-G-S','Connector_PinHeader_2.54mm','PinHeader_1x02_P2.54mm_Vertical',[87,50],{1:'FPGA_EN1',2:'GND'},note='Fit shunt to DISABLE module; open enables on-board sequence')
part('JP81','TZ_JP','TSW-102-07-G-S','Connector_PinHeader_2.54mm','PinHeader_1x02_P2.54mm_Vertical',[94,50],{1:'FPGA_CONFIG_RESET_N',2:'GND'},note='Fit shunt to request module configuration reset')
for ref,net,xy in [('R80','FPGA_JTAGEN',[123,36]),('R81','FPGA_NOSEQ',[89,40])]:
    body+=f'\n    {ref.lower()} = new P_10\n    trait {ref.lower()} has_designator<designator="{ref}">\n    {ref.lower()}.p1 ~ {net}\n    {ref.lower()}.p2 ~ GND\n'
    template=copy.deepcopy(next(x for x in parts if x['ref']=='R11'));template.update(ref=ref,xy=xy,section='08-trenz-carrier',note='FPGA JTAG selection / spare CPLD control idle pull-down');parts.append(template)
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
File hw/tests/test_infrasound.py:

import sys
from pathlib import Path
import unittest
sys.path.insert(0,str(Path(__file__).resolve().parents[1]/'tools'))
from infrasound_checks import PINS, MPN, verify


class InfrasoundTests(unittest.TestCase):
    def setUp(self):
        self.pins={**PINS, ('J1','18'):'GNSS_PPS',('J1','31'):'PI_SHUTDOWN_N',('J1','33'):'PI_HALTED'}
        self.pads={'1':(1.5,26), '2':(1.5,28.54), '3':(1.5,31.08), '4':(1.5,33.62)}

    def check(self, **changes):
        args=dict(pins=self.pins,pads=self.pads,pose=(270,False),mpn=MPN,dnp=False)
        args.update(changes)
        return verify(**args)

    def test_rejects_wrong_supply_and_swapped_bus(self):
        self.assertEqual(self.check()['additional_pi_pins'],0)
        for key in PINS:
            for net in ('PI_5V','FPGA_3V3','PI_I2C_SDA','WRONG'):
                with self.subTest(key=key,net=net),self.assertRaises(ValueError):
                    self.check(pins={**self.pins,key:net})

    def test_rejects_reversed_package_and_wrong_variant(self):
        for pose in ((90,False),(270,True),(0,False)):
            with self.assertRaises(ValueError):self.check(pose=pose)
        with self.assertRaises(ValueError):self.check(pads={**self.pads,'1':self.pads['4'],'4':self.pads['1']})
        with self.assertRaises(ValueError):self.check(mpn=MPN.replace('NI3F','NI5F'))
        with self.assertRaises(ValueError):self.check(dnp=True)

    def test_rejects_consumed_power_control_pin(self):
        for pin in ('18','31','33'):
            with self.assertRaises(ValueError):self.check(pins={**self.pins,('J1',pin):'I2C_SDA'})

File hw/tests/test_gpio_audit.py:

"""Fault injection for GPIO mapping: exercise known wiring hazards."""
import sys, unittest
from pathlib import Path
sys.path.insert(0, str(Path(__file__).resolve().parents[1] / 'tools'))
import gpio_audit as audit
import pcbnew

class GPIOFaultTests(unittest.TestCase):
    @classmethod
    def setUpClass(cls):
        board = pcbnew.LoadBoard(str(audit.ROOT / 'hw/groundlark-fpga-hat/layout/trenz_hat/trenz_hat.kicad_pcb'))
        cls.original = {(f.GetReference(),p.GetNumber()):p.GetNetname()
                        for f in board.GetFootprints() for p in f.Pads() if p.GetNumber()}

    def setUp(self):
        self.pins = self.original.copy()

    def test_valid_compiled_circuit(self):
        report=audit.check(self.pins)
        self.assertEqual(report['exposed_gpio'],0)
        self.assertEqual(report['unused_user_gpio'],149)

    def test_atomic_footprint_uuid_repair(self):
        from kicad_support import unique_ids
        b=pcbnew.BOARD()
        original=pcbnew.FootprintLoad(str(audit.ROOT/'hw/shared/elec'),'Package_SO__TSSOP-16_4.4x5mm_P0.65mm')
        for ref in ('U100','U101'):
            f=pcbnew.FOOTPRINT(original)
            f.SetReference(ref);b.Add(f)
        ids=lambda:[q.m_Uuid.AsString() for f in b.GetFootprints() for q in f.Pads()]
        self.assertNotEqual(len(ids()),len(set(ids())))
        unique_ids(b)
        repaired=ids()
        self.assertEqual(len(repaired),len(set(repaired)))
        unique_ids(b)
        self.assertEqual(ids(),repaired)

    def test_save_preserves_project_rules(self):
        import json, tempfile
        from kicad_support import save_board
        with tempfile.TemporaryDirectory() as tmp:
            path=Path(tmp)/'rules.kicad_pcb'
            project=path.with_suffix('.kicad_pro')
            content=json.dumps({'net_settings':{'classes':[{'name':'Default','clearance':0.15}]}}).encode()
            project.write_bytes(content)
            save_board(path,pcbnew.BOARD())
            self.assertEqual(project.read_bytes(),content)

    def test_old_grounded_gpio(self):
        self.pins['J80','32'] = 'GND'  # Module JM1.31, B16_L22_P.
        with self.assertRaises(AssertionError): audit.check(self.pins)

    def test_old_grounded_ethernet(self):
        self.pins['J80','11'] = 'GND'  # Module JM1.12, PHY ETH_RD_N.
        with self.assertRaises(AssertionError): audit.check(self.pins)

    def test_reversed_mating_parity(self):
        self.pins['J81','21'],self.pins['J81','22'] = self.pins['J81','22'],self.pins['J81','21']
        with self.assertRaises(AssertionError): audit.check(self.pins)

    def test_missing_quad_connection(self):
        self.pins['U101','5'] = 'UNCONNECTED'
        with self.assertRaises(AssertionError): audit.check(self.pins)

    def test_wrong_reference_voltage(self):
        self.pins['U100','16'] = 'PI_5V'
        with self.assertRaises(AssertionError): audit.check(self.pins)

    def test_unintended_shared_gpio(self):
        self.pins['EXTRA','1'] = self.pins['J80','32']
        with self.assertRaises(AssertionError): audit.check(self.pins)

    def test_switch_bypass_is_rejected(self):
        self.pins['J84','1'] = 'JTAG_TCK'
        with self.assertRaises(AssertionError): audit.check(self.pins)

    def test_wrong_gate_pinout_is_rejected(self):
        self.pins['U103','2'],self.pins['U103','3'] = self.pins['U103','3'],self.pins['U103','2']
        with self.assertRaises(AssertionError): audit.check(self.pins)

    def test_missing_safe_start_bias_is_rejected(self):
        self.pins['R107','2'] = 'PI_3V3'
        with self.assertRaises(AssertionError): audit.check(self.pins)

    def test_parking_path_must_not_ground_pi_output(self):
        self.pins['U101','3'] = 'GND'
        with self.assertRaises(AssertionError): audit.check(self.pins)

if __name__ == '__main__': unittest.main()
